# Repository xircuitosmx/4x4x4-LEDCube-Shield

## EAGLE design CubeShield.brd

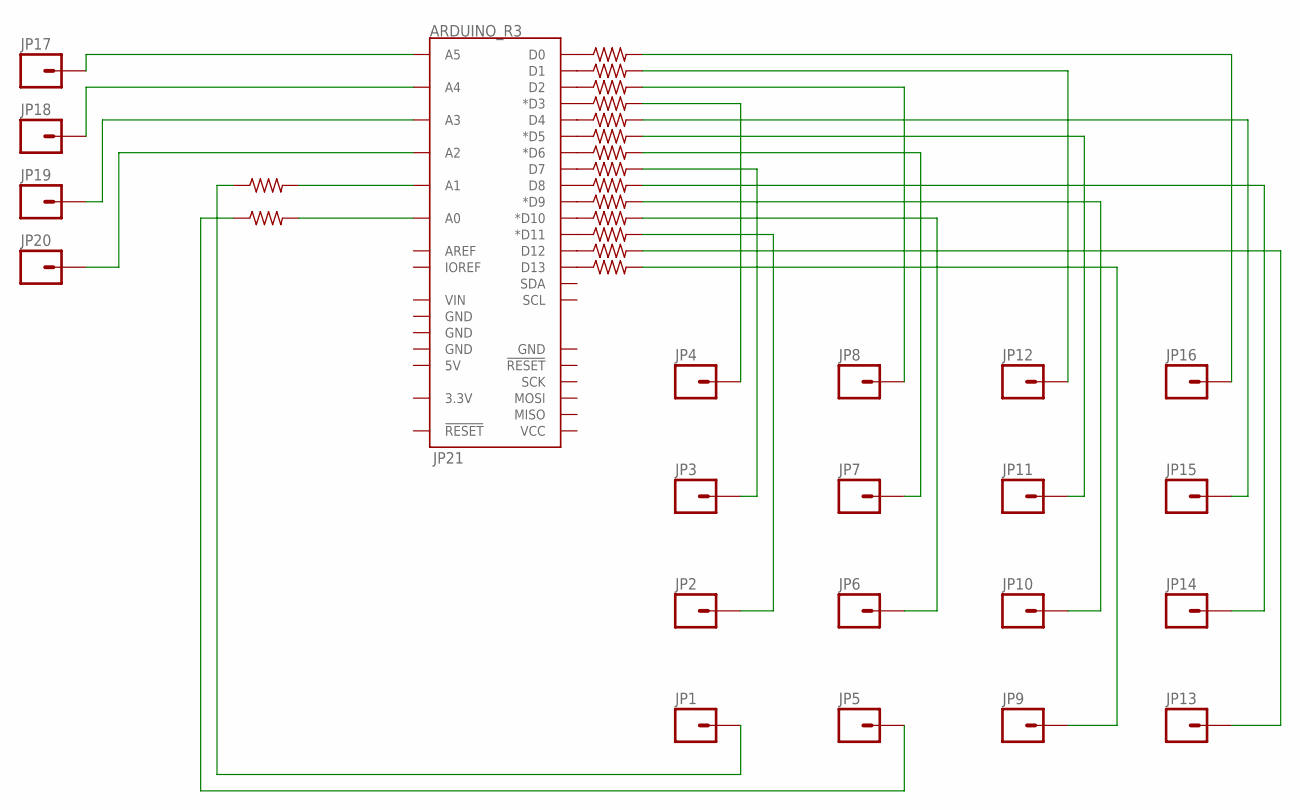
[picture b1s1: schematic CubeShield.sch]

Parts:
JP1, JP2, JP3, JP4, JP5, JP6, JP7, JP8, JP9, JP10, JP11, JP12, JP13, JP14, JP15, JP16, JP17, JP18, JP19, JP20: M01PTH_LONGPAD; 1X01_LONGPAD
JP21: ARDUINO_R3
R1, R2, R3, R4, R5, R6, R7, R8, R9, R10, R11, R12, R13, R14, R15, R16: R-US_0207/7; 0207/7

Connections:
unnamed: JP21.D0, R1.1
unnamed: JP21.D1, R2.1
unnamed: JP21.D2, R3.1
unnamed: JP21.D3 (*D3), R4.1
unnamed: JP21.D4, R5.1
unnamed: JP21.D5 (*D5), R6.1
unnamed: JP21.D6 (*D6), R7.1
unnamed: JP21.D7, R8.1
unnamed: JP21.D8, R9.1
unnamed: JP21.D9 (*D9), R10.1
unnamed: JP21.D10 (*D10), R11.1
unnamed: JP21.D11 (*D11), R12.1
unnamed: JP21.D12, R13.1
unnamed: JP21.D13, R14.1
unnamed: JP16.1, R1.2
unnamed: JP12.1, R2.2
unnamed: JP8.1, R3.2
unnamed: JP4.1, R4.2
unnamed: JP15.1, R5.2
unnamed: JP11.1, R6.2
unnamed: JP7.1, R7.2
unnamed: JP3.1, R8.2
unnamed: JP14.1, R9.2
unnamed: JP10.1, R10.2
unnamed: JP6.1, R11.2
unnamed: JP2.1, R12.2
unnamed: JP21.A0, R15.2
unnamed: JP21.A1, R16.2
unnamed: JP13.1, R13.2
unnamed: JP9.1, R14.2
unnamed: JP5.1, R15.1
unnamed: JP1.1, R16.1
unnamed: JP17.1, JP21.A5
unnamed: JP18.1, JP21.A4
unnamed: JP19.1, JP21.A3
unnamed: JP20.1, JP21.A2

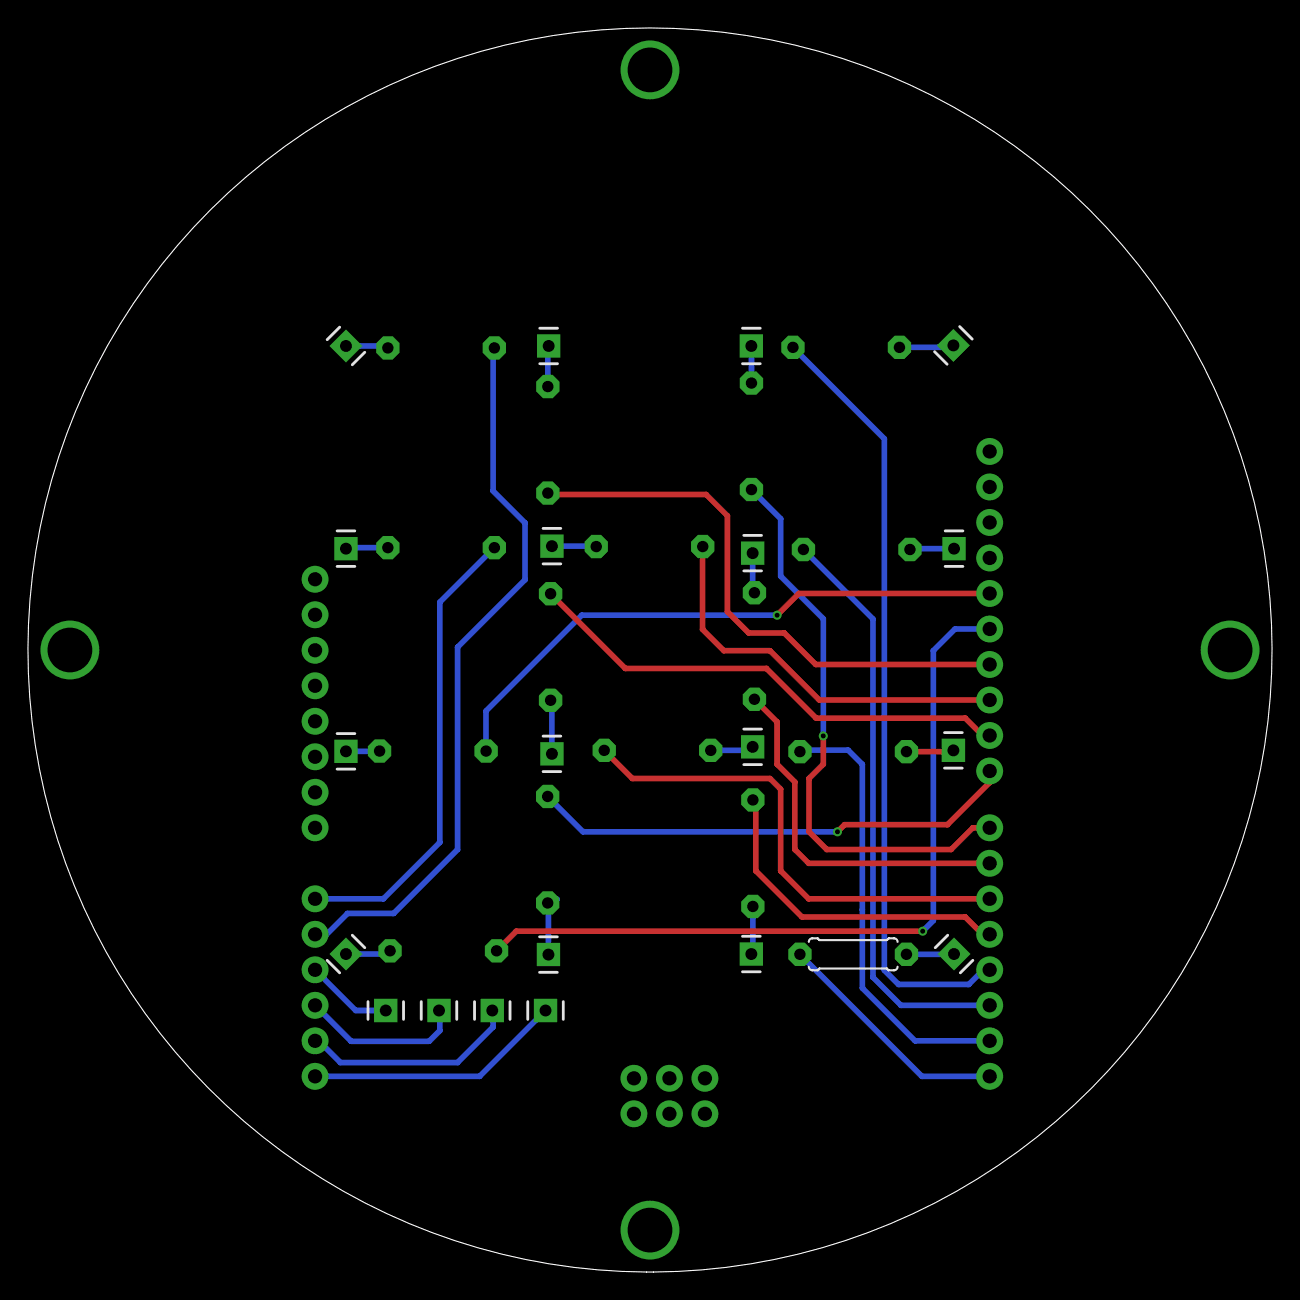
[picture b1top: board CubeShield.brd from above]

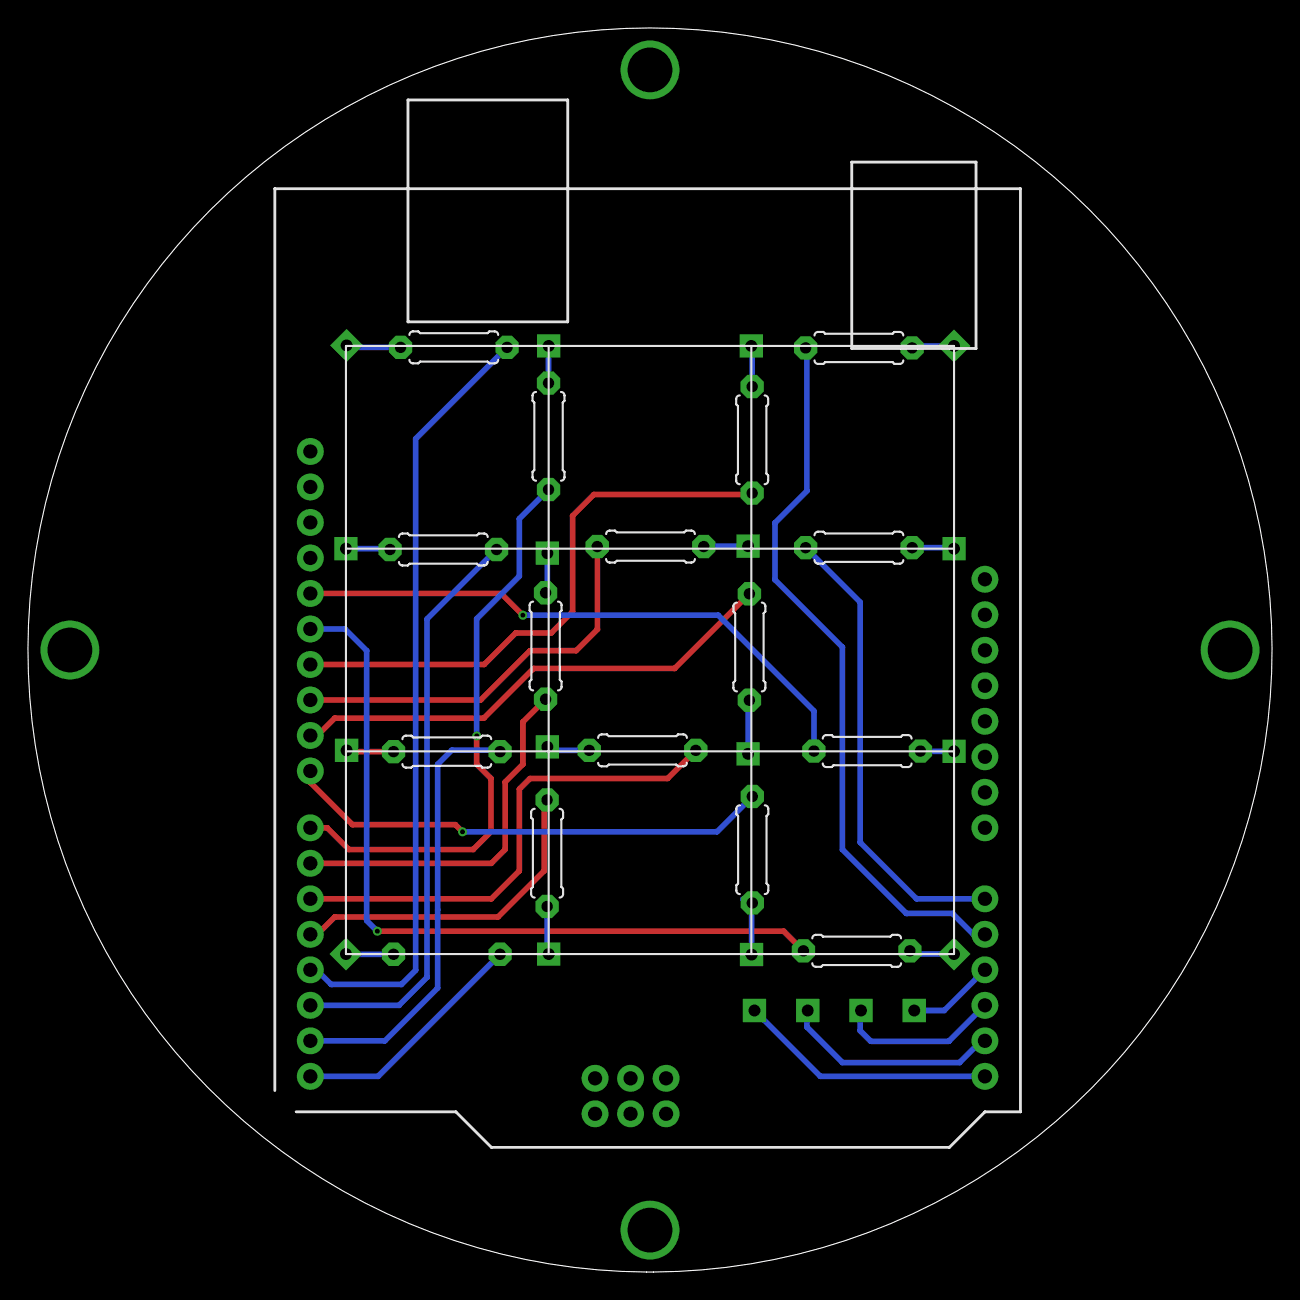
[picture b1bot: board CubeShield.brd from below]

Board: 2 copper layers, 89.0 x 89.0 mm, 37 parts (15 on the bottom side), 36 nets.

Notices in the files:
parts and their libraries:
SparkFun-Boards: Licensing: Creative Commons ShareAlike 4.0 International - https://creativecommons.org/licenses/by-sa/4.0
